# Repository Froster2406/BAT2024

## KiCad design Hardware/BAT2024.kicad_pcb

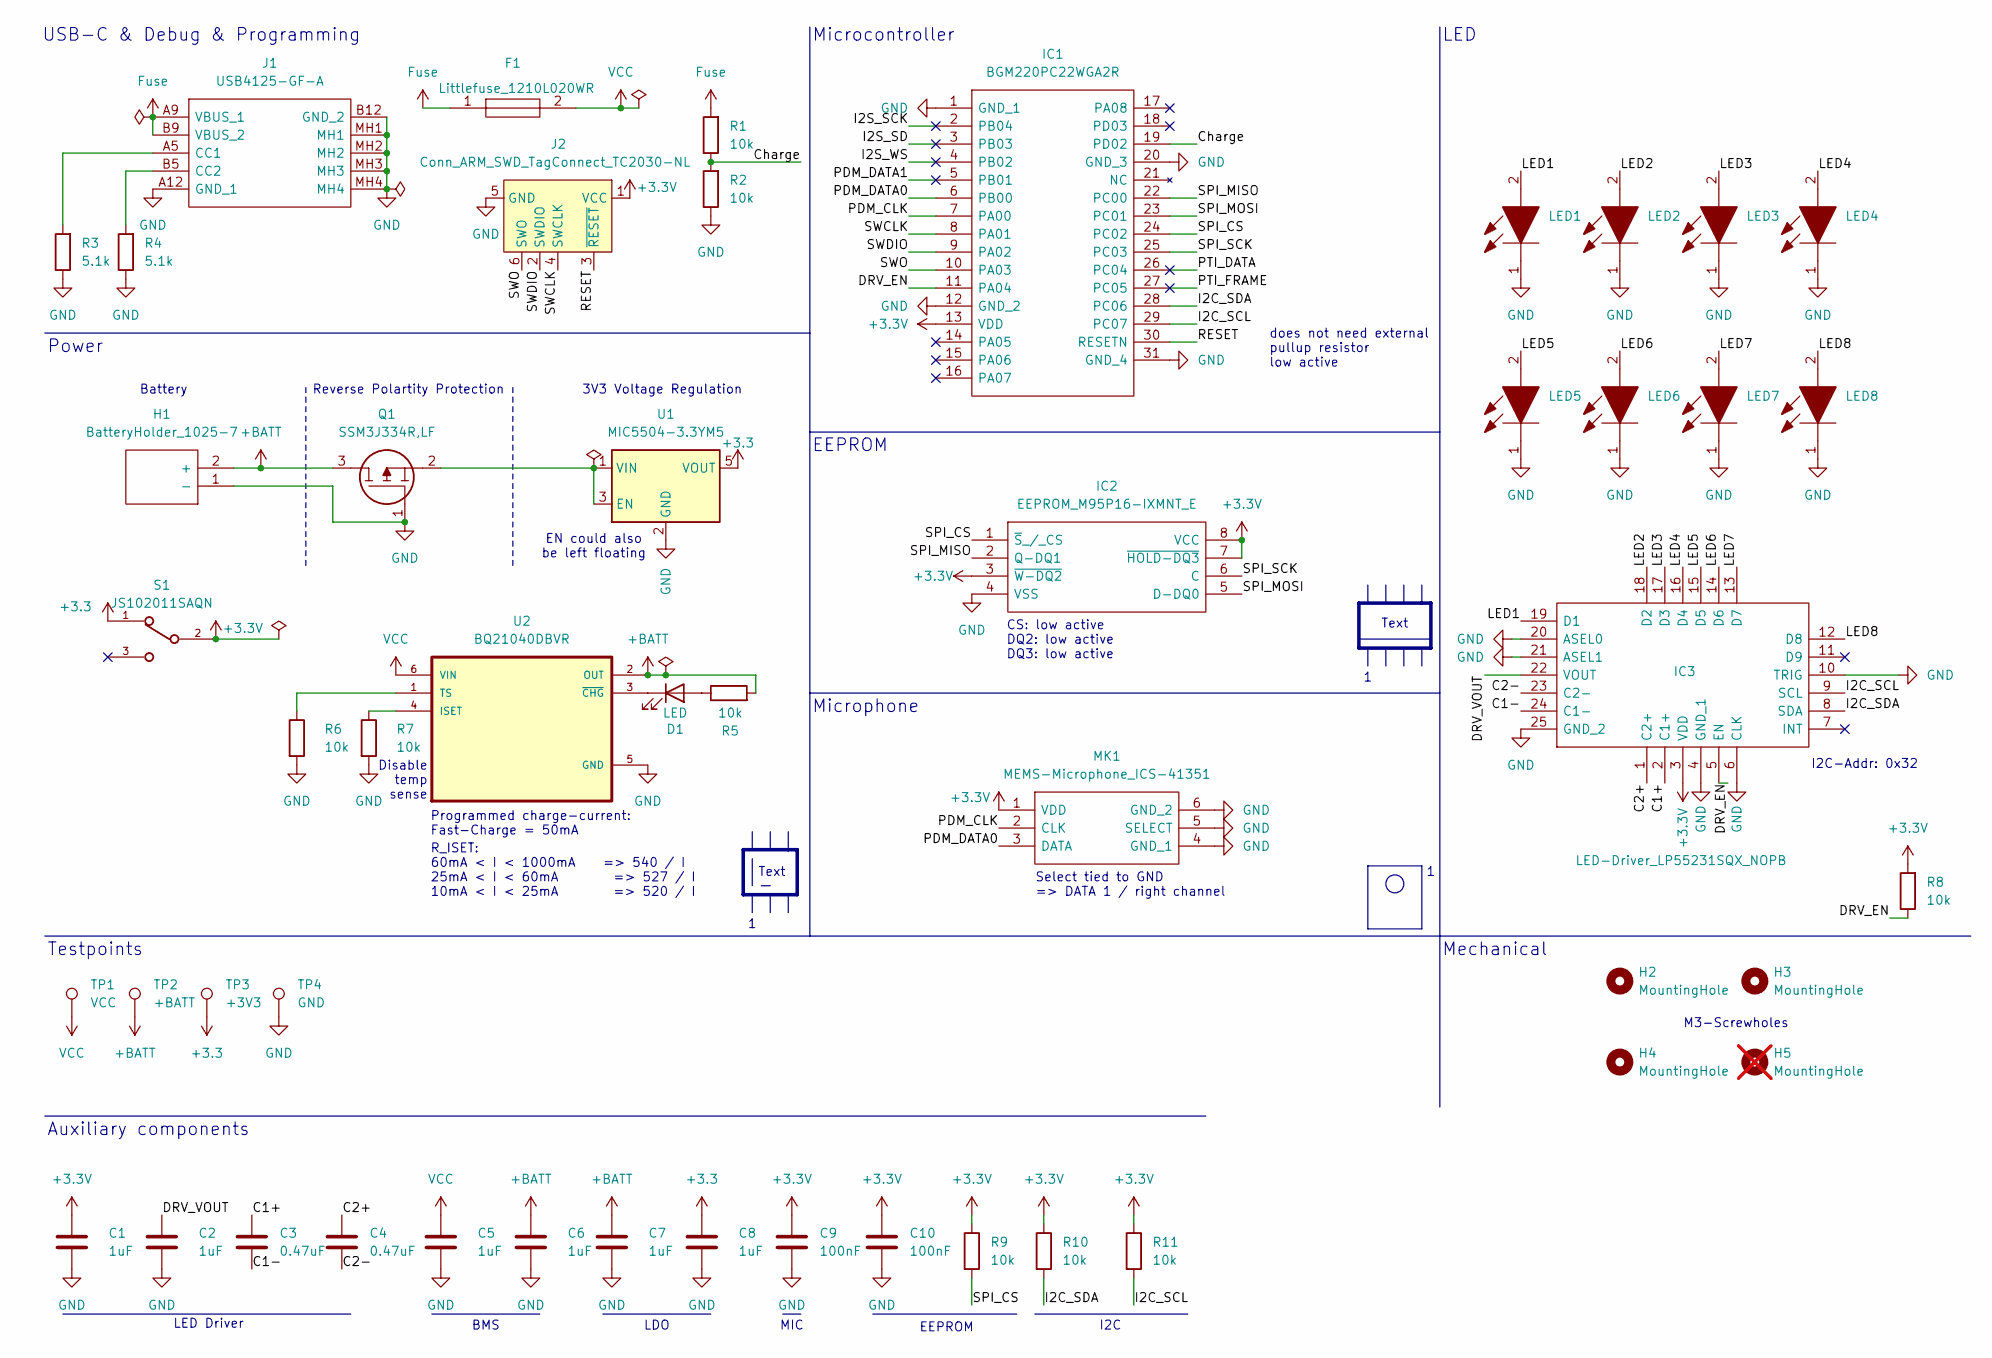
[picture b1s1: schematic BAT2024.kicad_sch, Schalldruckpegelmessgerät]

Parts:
C1, C2, C5, C6, C7, C8: 1uF; C_0603_1608Metric_Pad1.08x0.95mm_HandSolder
C3, C4: 0.47uF; C_0603_1608Metric_Pad1.08x0.95mm_HandSolder
C9, C10: 100nF; C_0603_1608Metric_Pad1.08x0.95mm_HandSolder
D1: LED; LED_0603_1608Metric_Pad1.05x0.95mm_HandSolder
F1: Littlefuse_1210L020WR; Littlefuse_FUSC3226X100N; Mouser Part Number 576-1210L020WR
H1: BatteryHolder_1025-7; BatteryHolder_10257; Mouser Part Number 534-1025-7
H2, H3, H4: MountingHole; MountingHole_3.2mm_M3
H5: MountingHole; MountingHole_3.2mm_M3; not fitted
IC1: BGM220PC22WGA2R; Mouser Part Number 634-BGM220PC22WGA2R
IC2: EEPROM_M95P16-IXMNT_E; EEPROM_SOIC127P600X175-8L; Mouser Part Number 511-M95P16-IXMNT/E
IC3: LED-Driver_LP55231SQX_NOPB; LED-Driver-QFN50P400X400X80-25N; Mouser Part Number 595-LP55231SQX/NOPB
J1: USB4125-GF-A; USB4125GFA; Mouser Part Number 640-USB4125-GF-A
J2: Conn_ARM_SWD_TagConnect_TC2030-NL; Tag-Connect_TC2030-IDC-NL_2x03_P1.27mm_Vertical
LED1, LED2, LED3, LED4, LED5, LED6, LED7, LED8: LED_XZCM2CRK53WA-8VF; LEDM168X110N; Manufacturer_Part_Number XZCM2CRK53WA-8VF
MK1: MEMS-Microphone_ICS-41351; MEMS-Mikrofon_ICS41351; Mouser Part Number 410-ICS-41351
Q1: SSM3J334R,LF; SSM3J334RLF; Mouser Part Number 757-SSM3J334RLF
R1, R2, R5, R6, R7, R8, R9, R10, R11: 10k; R_0603_1608Metric_Pad0.98x0.95mm_HandSolder
R3, R4: 5.1k; R_0603_1608Metric_Pad0.98x0.95mm_HandSolder
S1: JS102011SAQN; C-K_Switch_JS102011SAQN; DigiKey_Part_Number 401-1999-2-ND
TP1: VCC; TestPoint_Pad_D1.0mm
TP2: +BATT; TestPoint_Pad_D1.0mm
TP3: +3V3; TestPoint_Pad_D1.0mm
TP4: GND; TestPoint_Pad_D1.0mm
U1: MIC5504-3.3YM5; SOT-23-5
U2: BQ21040DBVR; BatteryManagement_SOT95P280X145-6N

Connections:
+3.3: C8.1, S1.1, TP3.1, U1.5 (VOUT)
+3.3V: C1.1, C9.1, C10.1, IC1.13 (VDD), IC2.3 (~W-DQ2), IC2.7 (~HOLD-DQ3), IC2.8 (VCC), IC3.3 (VDD), J2.1 (VCC), MK1.1 (VDD), R8.2, R9.1, R10.1, R11.1, S1.2
+BATT: C6.1, C7.1, H1.2 (+), Q1.3, R5.2, TP2.1, U2.2 (OUT)
/C1+: C3.1, IC3.2 (C1+)
/C1-: C3.2, IC3.24 (C1-)
/C2+: C4.1, IC3.1 (C2+)
/C2-: C4.2, IC3.23 (C2-)
/Charge: IC1.19 (PD02), R1.1, R2.2
/DRV_EN: IC1.11 (PA04), IC3.5 (EN), R8.1
/DRV_VOUT: C2.1, IC3.22 (VOUT)
/I2C_SCL: IC1.29 (PC07), IC3.9 (SCL), R11.2
/I2C_SDA: IC1.28 (PC06), IC3.8 (SDA), R10.2
/I2S_SCK: IC1.2 (PB04)
/I2S_SD: IC1.3 (PB03)
/I2S_WS: IC1.4 (PB02)
/LED1: IC3.19 (D1), LED1.2
/LED2: IC3.18 (D2), LED2.2
/LED3: IC3.17 (D3), LED3.2
/LED4: IC3.16 (D4), LED4.2
/LED5: IC3.15 (D5), LED5.2
/LED6: IC3.14 (D6), LED6.2
/LED7: IC3.13 (D7), LED7.2
/LED8: IC3.12 (D8), LED8.2
/PDM_CLK: IC1.7 (PA00), MK1.2 (CLK)
/PDM_DATA0: IC1.6 (PB00), MK1.3 (DATA)
/PDM_DATA1: IC1.5 (PB01)
/PTI_DATA: IC1.26 (PC04)
/PTI_FRAME: IC1.27 (PC05)
/RESET: IC1.30 (RESETN), J2.3 (~RESET)
/SPI_CS: IC1.24 (PC02), IC2.1 (~S_/_CS), R9.2
/SPI_MISO: IC1.22 (PC00), IC2.2 (Q-DQ1)
/SPI_MOSI: IC1.23 (PC01), IC2.5 (D-DQ0)
/SPI_SCK: IC1.25 (PC03), IC2.6 (C)
/SWCLK: IC1.8 (PA01), J2.4 (SWCLK)
/SWDIO: IC1.9 (PA02), J2.2 (SWDIO)
/SWO: IC1.10 (PA03), J2.6 (SWO)
Fuse: F1.1, J1.A9 (VBUS_1), J1.B9 (VBUS_2), R1.2
GND: C1.2, C2.2, C5.2, C6.2, C7.2, C8.2, C9.2, C10.2, H1.1 (-), IC1.1 (GND_1), IC1.12 (GND_2), IC1.20 (GND_3), IC1.31 (GND_4), IC2.4 (VSS), IC3.4 (GND_1), IC3.6 (CLK), IC3.10 (TRIG), IC3.20 (ASEL0), IC3.21 (ASEL1), IC3.25 (GND_2), J1.A12 (GND_1), J1.B12 (GND_2), J1.MH1, J1.MH2, J1.MH3, J1.MH4, J2.5 (GND), LED1.1, LED2.1, LED3.1, LED4.1, LED5.1, LED6.1, LED7.1, LED8.1, MK1.4 (GND_1), MK1.5 (SELECT), MK1.6 (GND_2), Q1.1, R2.1, R3.1, R4.1, R6.2, R7.2, TP4.1, U1.2 (GND), U2.5 (GND)
unnamed: D1.2 (A), R5.1
unnamed: D1.1 (K), U2.3 (~CHG)
unnamed: J1.A5 (CC1), R3.2
unnamed: J1.B5 (CC2), R4.2
unnamed: Q1.2, U1.1 (VIN), U1.3 (EN)
unnamed: R7.1, U2.4 (ISET)
unnamed: R6.1, U2.1 (TS)
VCC: C5.1, F1.2, TP1.1, U2.6 (VIN)

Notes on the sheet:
Programmed charge-current: Fast-Charge = 50mA
Select tied to GND => DATA 1 / right channel
I2C
Disable temp sense
Text
Reverse Polartity Protection
MIC
LDO
Power
Testpoints
EEPROM
Microphone
does not need external pullup resistor low active
BMS
M3-Screwholes
CS: low active DQ2: low active DQ3: low active
LED Driver
Mechanical
EN could also be left floating
Microcontroller
I2C-Addr: 0x32
LED
USB-C & Debug & Programming
Battery
3V3 Voltage Regulation
R_ISET: 60mA < I < 1000mA => 540 / I 25mA < I < 60mA => 527 / I 10mA < I < 25mA => 520 / I
Auxiliary components

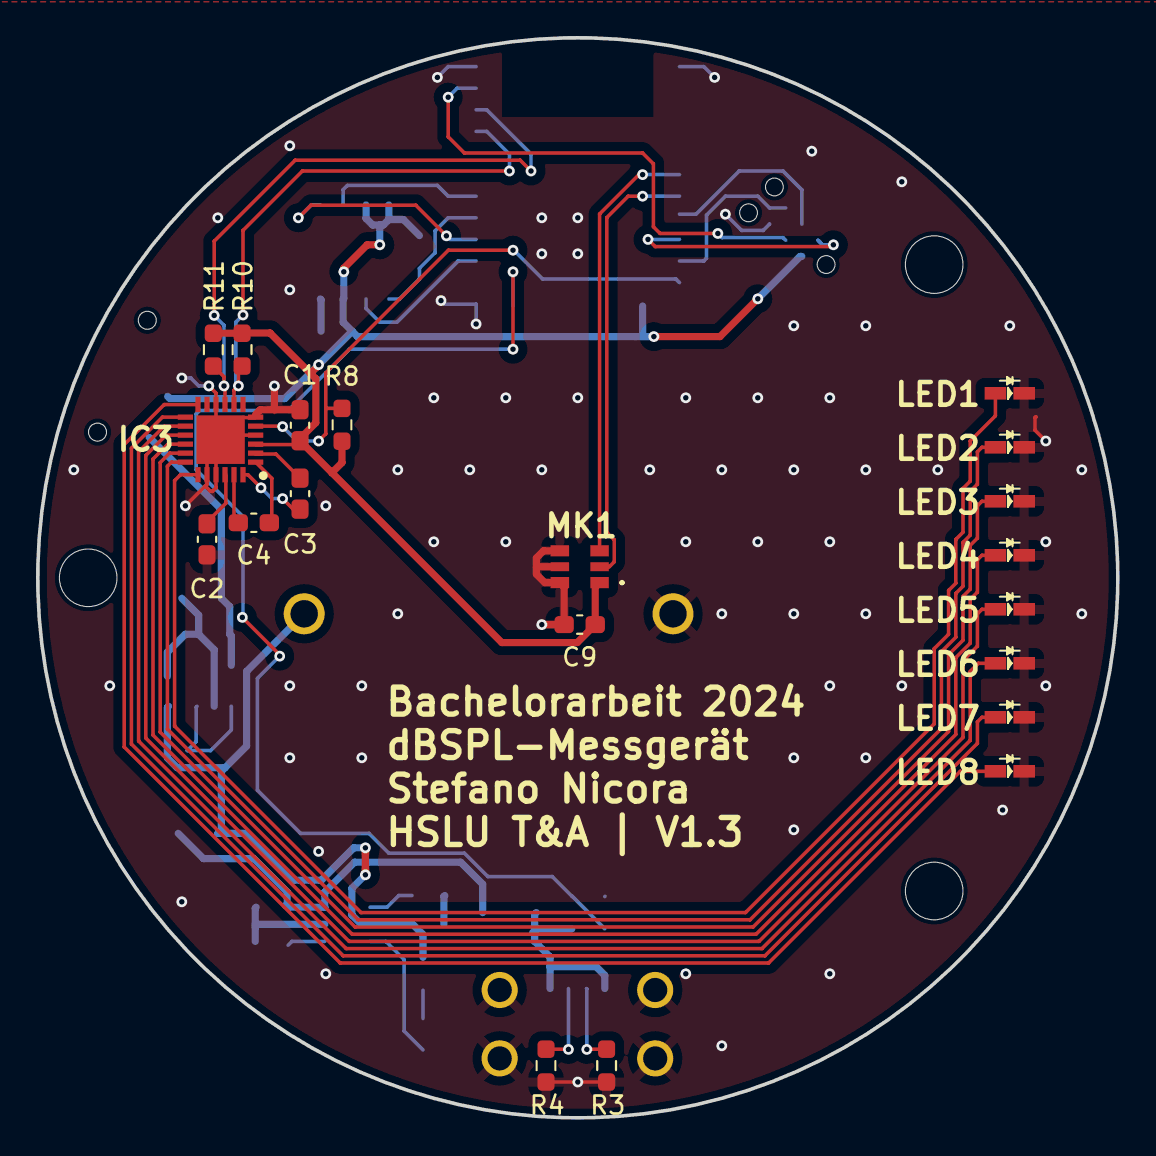
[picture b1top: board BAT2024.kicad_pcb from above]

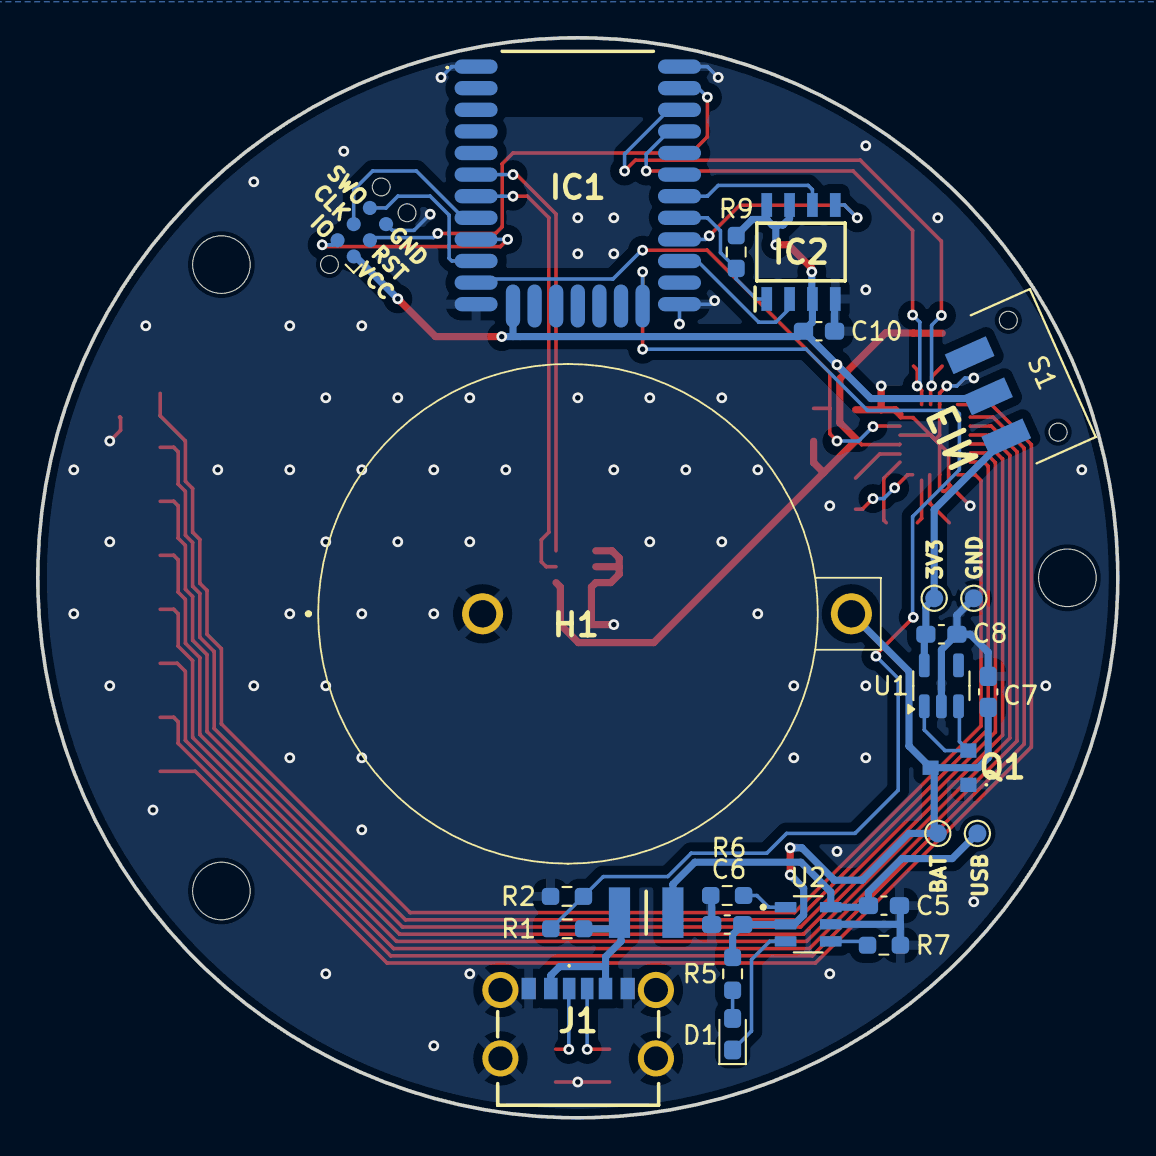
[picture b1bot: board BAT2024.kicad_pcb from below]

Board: 2 copper layers, 60.0 x 60.0 mm, 49 parts (29 on the bottom side), 40 nets.

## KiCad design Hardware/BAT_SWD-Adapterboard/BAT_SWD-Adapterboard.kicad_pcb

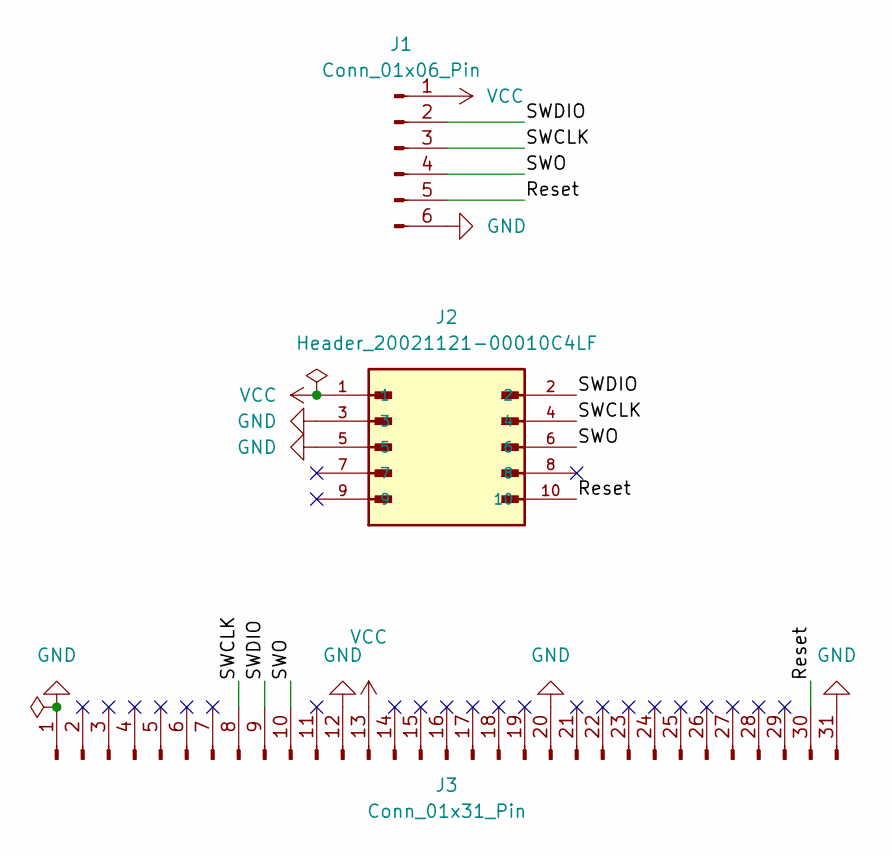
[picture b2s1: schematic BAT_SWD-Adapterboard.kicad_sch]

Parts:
J1: Conn_01x06_Pin; PinHeader_2x03_P2.54mm_Vertical
J2: Header_20021121-00010C4LF; AMPHENOL_20021121-00010C4LF; PARTREV R
J3: Conn_01x31_Pin; BGM220PC22WGA2R_castellated-holes

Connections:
/Reset: J1.5, J2.10, J3.30
/SWCLK: J1.3, J2.4, J3.8
/SWDIO: J1.2, J2.2, J3.9
/SWO: J1.4, J2.6, J3.10
GND: J1.6, J2.3, J2.5, J3.1, J3.12, J3.20, J3.31
VCC: J1.1, J2.1, J3.13

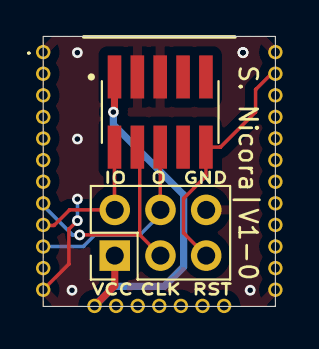
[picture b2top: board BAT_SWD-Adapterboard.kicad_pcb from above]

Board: 2 copper layers, 12.9 x 15.0 mm, 3 parts (0 on the bottom side), 6 nets.

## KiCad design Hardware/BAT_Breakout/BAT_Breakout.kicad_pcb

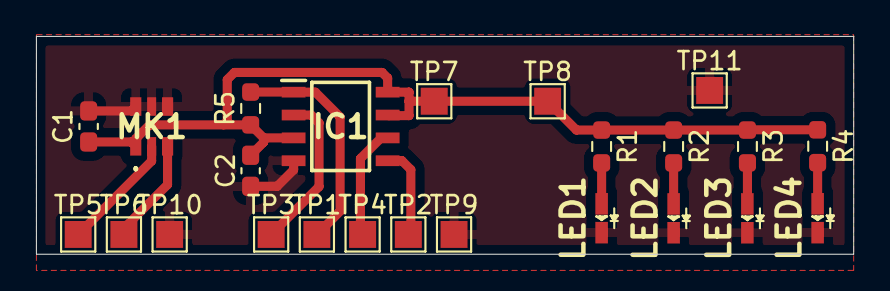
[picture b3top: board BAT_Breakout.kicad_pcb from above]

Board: 2 copper layers, 45.4 x 12.1 mm, 24 parts (0 on the bottom side), 12 nets.

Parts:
C1, C2: 100nF; C_0603_1608Metric_Pad1.08x0.95mm_HandSolder
IC1: EEPROM_M95P16-IXMNT_E; EEPROM_SOIC127P600X175-8L
LED1, LED2, LED3, LED4: LED_XZCM2CRK53WA-8VF; LEDM168X110N
MK1: MEMS-Microphone_ICS-41351; MEMS-Mikrofon_ICS41351
R1, R2, R3, R4: R; R_0603_1608Metric_Pad0.98x0.95mm_HandSolder
R5: 10k; R_0603_1608Metric_Pad0.98x0.95mm_HandSolder
TP1: CS; TestPoint_Pad_1.5x1.5mm
TP2: MOSI; TestPoint_Pad_1.5x1.5mm
TP3: MISO; TestPoint_Pad_1.5x1.5mm
TP4: CLK; TestPoint_Pad_1.5x1.5mm
TP5: PDM_CLK; TestPoint_Pad_1.5x1.5mm
TP6: PDM_DATA0; TestPoint_Pad_1.5x1.5mm
TP7, TP8: +3V3; TestPoint_Pad_1.5x1.5mm
TP9, TP10, TP11: GND; TestPoint_Pad_1.5x1.5mm

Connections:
+3.3V: C1.1, C2.1, IC1.3 (~W-DQ2), IC1.7 (~HOLD-DQ3), IC1.8 (VCC), MK1.1 (VDD), R1.1, R2.1, R3.1, R4.1, R5.1, TP7.1, TP8.1
/PDM_CLK: MK1.2 (CLK), TP5.1
/PDM_DATA0: MK1.3 (DATA), TP6.1
/SPI_CS: IC1.1 (~S_/_CS), R5.2, TP1.1
/SPI_MISO: IC1.2 (Q-DQ1), TP3.1
/SPI_MOSI: IC1.5 (D-DQ0), TP2.1
/SPI_SCK: IC1.6 (C), TP4.1
GND: C1.2, C2.2, IC1.4 (VSS), LED1.1, LED2.1, LED3.1, LED4.1, MK1.4 (GND_1), MK1.5 (SELECT), MK1.6 (GND_2), TP9.1, TP10.1, TP11.1
unnamed: LED1.2, R1.2
unnamed: LED2.2, R2.2
unnamed: LED3.2, R3.2
unnamed: LED4.2, R4.2

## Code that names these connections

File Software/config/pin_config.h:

#ifndef PIN_CONFIG_H
#define PIN_CONFIG_H

// $[CMU]
// [CMU]$

// $[PRS.ASYNCH0]
// [PRS.ASYNCH0]$

// $[PRS.ASYNCH1]
// [PRS.ASYNCH1]$

// $[PRS.ASYNCH2]
// [PRS.ASYNCH2]$

// $[PRS.ASYNCH3]
// [PRS.ASYNCH3]$

// $[PRS.ASYNCH4]
// [PRS.ASYNCH4]$

// $[PRS.ASYNCH5]
// [PRS.ASYNCH5]$

// $[PRS.ASYNCH6]
// [PRS.ASYNCH6]$

// $[PRS.ASYNCH7]
// [PRS.ASYNCH7]$

// $[PRS.ASYNCH8]
// [PRS.ASYNCH8]$

// $[PRS.ASYNCH9]
// [PRS.ASYNCH9]$

// $[PRS.ASYNCH10]
// [PRS.ASYNCH10]$

// $[PRS.ASYNCH11]
// [PRS.ASYNCH11]$

// $[PRS.SYNCH0]
// [PRS.SYNCH0]$

// $[PRS.SYNCH1]
// [PRS.SYNCH1]$

// $[PRS.SYNCH2]
// [PRS.SYNCH2]$

// $[PRS.SYNCH3]
// [PRS.SYNCH3]$

// $[GPIO]
// GPIO SWCLK on PA01
#ifndef GPIO_SWCLK_PORT                         
#define GPIO_SWCLK_PORT                          gpioPortA
#endif
#ifndef GPIO_SWCLK_PIN                          
#define GPIO_SWCLK_PIN                           1
#endif

// GPIO SWDIO on PA02
#ifndef GPIO_SWDIO_PORT                         
#define GPIO_SWDIO_PORT                          gpioPortA
#endif
#ifndef GPIO_SWDIO_PIN                          
#define GPIO_SWDIO_PIN                           2
#endif

// GPIO TRACEDATA0 on PA03
#ifndef GPIO_TRACEDATA0_PORT                    
#define GPIO_TRACEDATA0_PORT                     gpioPortA
#endif
#ifndef GPIO_TRACEDATA0_PIN                     
#define GPIO_TRACEDATA0_PIN                      3
#endif

// [GPIO]$

// $[TIMER0]
// [TIMER0]$

// $[TIMER1]
// [TIMER1]$

// $[TIMER2]
// [TIMER2]$

// $[TIMER3]
// [TIMER3]$

// $[TIMER4]
// [TIMER4]$

// $[USART0]
// USART0 CLK on PC03
#ifndef USART0_CLK_PORT                         
#define USART0_CLK_PORT                          gpioPortC
#endif
#ifndef USART0_CLK_PIN                          
#define USART0_CLK_PIN                           3
#endif

// USART0 CS on PC02
#ifndef USART0_CS_PORT                          
#define USART0_CS_PORT                           gpioPortC
#endif
#ifndef USART0_CS_PIN                           
#define USART0_CS_PIN                            2
#endif

// USART0 RX on PC00
#ifndef USART0_RX_PORT                          
#define USART0_RX_PORT                           gpioPortC
#endif
#ifndef USART0_RX_PIN                           
#define USART0_RX_PIN                            0
#endif

// USART0 TX on PC01
#ifndef USART0_TX_PORT                          
#define USART0_TX_PORT                           gpioPortC
#endif
#ifndef USART0_TX_PIN                           
#define USART0_TX_PIN                            1
#endif

// [USART0]$

// $[USART1]
// [USART1]$

// $[I2C1]
// [I2C1]$

// $[PDM]
// [PDM]$

// $[LETIMER0]
// [LETIMER0]$

// $[IADC0]
// [IADC0]$

// $[I2C0]
// I2C0 SCL on PC07
#ifndef I2C0_SCL_PORT                           
#define I2C0_SCL_PORT                            gpioPortC
#endif
#ifndef I2C0_SCL_PIN                            
#define I2C0_SCL_PIN                             7
#endif

// I2C0 SDA on PC06
#ifndef I2C0_SDA_PORT                           
#define I2C0_SDA_PORT                            gpioPortC
#endif
#ifndef I2C0_SDA_PIN                            
#define I2C0_SDA_PIN                             6
#endif

// [I2C0]$

// $[EUART0]
// [EUART0]$

// $[PTI]
// PTI DFRAME on PC05
#ifndef PTI_DFRAME_PORT                         
#define PTI_DFRAME_PORT                          gpioPortC
#endif
#ifndef PTI_DFRAME_PIN                          
#define PTI_DFRAME_PIN                           5
#endif

// PTI DOUT on PC04
#ifndef PTI_DOUT_PORT                           
#define PTI_DOUT_PORT                            gpioPortC
#endif
#ifndef PTI_DOUT_PIN                            
#define PTI_DOUT_PIN                             4
#endif

// [PTI]$

// $[MODEM]
// [MODEM]$

// $[CUSTOM_PIN_NAME]
#ifndef _PORT                                   
#define _PORT                                    gpioPortA
#endif
#ifndef _PIN                                    
#define _PIN                                     0
#endif

#ifndef DRV_EN_PORT                             
#define DRV_EN_PORT                              gpioPortA
#endif
#ifndef DRV_EN_PIN                              
#define DRV_EN_PIN                               4
#endif

#ifndef SPI_MISO_PORT                           
#define SPI_MISO_PORT                            gpioPortC
#endif
#ifndef SPI_MISO_PIN                            
#define SPI_MISO_PIN                             0
#endif

#ifndef SPI_MOSI_PORT                           
#define SPI_MOSI_PORT                            gpioPortC
#endif
#ifndef SPI_MOSI_PIN                            
#define SPI_MOSI_PIN                             1
#endif

#ifndef SPI_CS_PORT                             
#define SPI_CS_PORT                              gpioPortC
#endif
#ifndef SPI_CS_PIN                              
#define SPI_CS_PIN                               2
#endif

#ifndef SPI_CLK_PORT                            
#define SPI_CLK_PORT                             gpioPortC
#endif
#ifndef SPI_CLK_PIN                             
#define SPI_CLK_PIN                              3
#endif

// [CUSTOM_PIN_NAME]$

#endif // PIN_CONFIG_H

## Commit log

2024-02-17 created initial folders for HW, SW and documentation
2024-02-27 Add LaTeX-Basefile; update .gitignore
2024-02-27 remove content.txt
2024-02-27 Doku stand: 20240227
2024-02-27 Add table microcontroller-vergleich
2024-02-27 Add datasheets for microcontrollers that could be used
2024-02-28 finalized comparison table for microcontroller
2024-02-28 Add I2S-Image
2024-02-28 Doku Stand: 20240228
2024-03-04 moved microcontroller datasheets into folder
2024-03-04 Doku Stand: 20240304
2024-03-04 Add datasheets
2024-03-04 Add new images and tables for documentation purpose
2024-03-04 Add initial files for PCB design
2024-03-05 Add PDF-Files for PCB V1.0
2024-03-05 Add material list for PCB V1.0
2024-03-05 Created basic library for PCB-Design
2024-03-05 Updated PCB-Library with missing parts + linked symbols with footprints
2024-03-09 Finalized schematic V1.0; minor changes to symbol library
2024-03-10 Add temporary layout of footprints on PCB; generate placement-pdf
2024-03-12 Created first layout
2024-03-12 Generated gerber-files
2024-03-13 Add breakout-board to test SPI, PDM and LEDs
2024-03-13 Add software baseproject
2024-03-14 Removed most vias for stitching, minor general adjustments for layout
2024-03-16 Doku stand: 20240316
2024-03-20 Doku stand: 20240320
2024-03-20 Created V1-0 of adapterboard to convert dev-board to SWD programmer
2024-03-20 updated pcb library
2024-03-20 removed backup files
2024-03-20 Add basic files for software development
2024-03-24 Add new functions to SPI
2024-03-24 Minor adjustments to SWD-Adapterboard
2024-03-24 Doku stand: 20240324
2024-03-24 add missing doku files
2024-03-25 Add IC outline to schematic; Add iBom for V1-1
2024-03-27 Add flowchart for I2C connection with LED driver IC
2024-03-28 Add I2C driver implementation to communicate with lp55231
2024-03-28 Created PCB V1-2; see documentation for changelog
2024-04-01 Doku stand: 20240401
2024-04-02 Add first version of LETIMER-driver
2024-04-02 Add basic file for GPIO-only manipulation
2024-04-02 Removed compiler optimization
2024-04-02 Add minor todos to documentation
2024-04-03 Doku stand: 20240403
2024-04-03 Add V1 of presentation
2024-04-08 Updated presentation
2024-04-14 Add new images and minor adjustments to PPP
2024-04-14 Add exported matlab filter
2024-04-14 Add a-weighting filter test
2024-04-15 Doku stand: 20240415
2024-04-15 Add new defines
2024-04-15 Add support for defines
2024-04-20 Add V1-3 of PCB. See changelog for more information
2024-04-21 Stand doku: 20240421
2024-04-24 Stand doku: 20240424
2024-04-27 Doku stand: 20240427
2024-04-28 Stand doku: 20240428
2024-04-29 Add time measurements for different function calls
2024-04-29 Add new section
2024-04-29 Add timer functionaliy to represent main loop
2024-04-29 Add logging string function
2024-04-29 Convert RTC time to actual timestamp (not unix time)
2024-04-29 Add new functions; convert all functions to blocking
2024-04-29 Add spi timing measurements
2024-05-04 Stand doku: 20240504
2024-05-05 Stand doku: 20240505
2024-05-09 Add semiworking PDM data aquisition
2024-05-11 Stand doku: 20240511
2024-05-11 Removed legacy code
2024-05-11 Add BOM V1-3
2024-05-13 Stand doku: 20240513
2024-05-18 Stand doku: 20240518
2024-05-19 add matlab files
2024-05-19 Add weighting filter
2024-05-19 Add app.c
2024-05-19 Stand doku: 20240519
2024-05-20 Doku stand: 20240520
2024-05-21 Stand doku: 20240521
2024-05-23 Doku stand: 20240523
2024-05-27 Doku stand: 20240527
2024-05-30 Doku V1-0
2024-05-30 Add filtercoefficients for reference
2024-05-31 Reworked documentation
2024-06-01 Minor adjustments to pdf; Add delivery files
2024-06-02 Updated sources to include date
2024-06-02 Final adjustments to documentation
2024-06-04 Equalized all function descriptions
2024-06-06 Minor changes to the documentation
2024-06-06 Minor tweaks to filter-implementation; finalized software
2024-06-18 Added pagenumbers
